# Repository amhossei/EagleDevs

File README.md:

# EagleDevs
Repository of my Eagle developments

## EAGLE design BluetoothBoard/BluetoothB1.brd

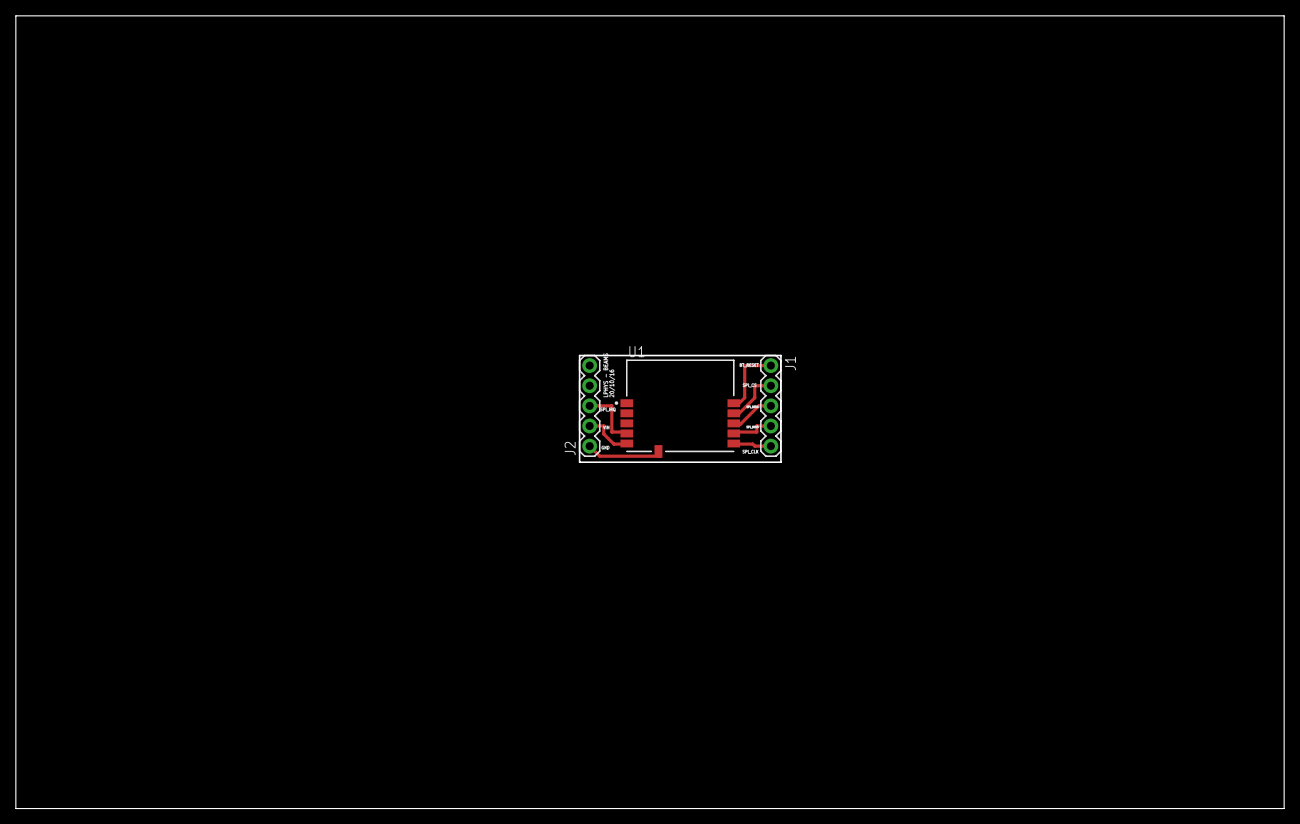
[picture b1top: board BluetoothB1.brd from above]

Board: 2 copper layers, 160.0 x 100.0 mm, 3 parts (0 on the bottom side), 8 nets.

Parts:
J1, J2: 1X05
U1: SPBTLE-RF; XCVR_SPBTLE-RF

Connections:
GND: J2.1, U1.6
unnamed: J1.5, U1.7
unnamed: J1.3, U1.9
unnamed: J1.2, U1.10
unnamed: J1.1, U1.11
unnamed: J2.2, U1.5
unnamed: J2.3, U1.4
SPIMISO: J1.4, U1.8

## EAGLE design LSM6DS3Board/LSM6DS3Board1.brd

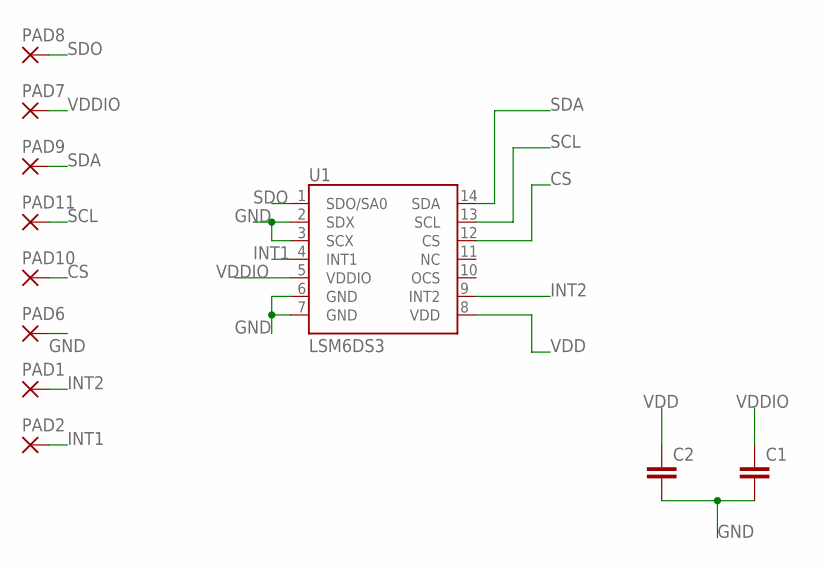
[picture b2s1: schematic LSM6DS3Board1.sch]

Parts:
C1, C2: C-EUC0603; C0603
PAD1, PAD2, PAD6, PAD7, PAD8, PAD9, PAD10, PAD11: 1,6/0,8
U1: LSM6DS3; LGA14L

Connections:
CS: PAD10.1, U1.12 (CS)
GND: C1.2, C2.2, PAD6.1, U1.2 (SDX), U1.3 (SCX), U1.6 (GND), U1.7 (GND)
INT1: PAD2.1, U1.4 (INT1)
INT2: PAD1.1, U1.9 (INT2)
SCL: PAD11.1, U1.13 (SCL)
SDA: PAD9.1, U1.14 (SDA)
SDO: PAD8.1, U1.1 (SDO/SA0)
VDD: C2.1, U1.8 (VDD)
VDDIO: C1.1, PAD7.1, U1.5 (VDDIO)

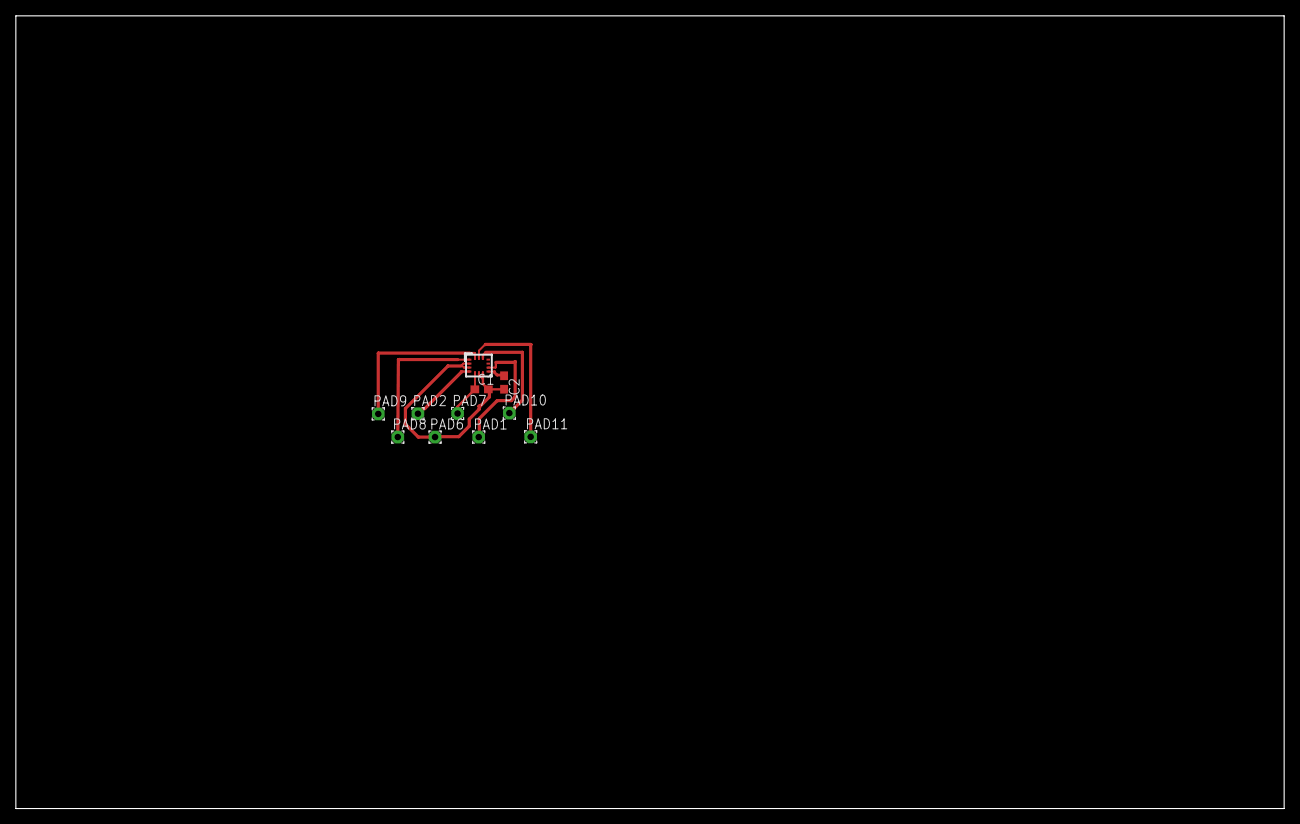
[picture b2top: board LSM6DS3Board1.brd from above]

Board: 2 copper layers, 160.0 x 100.0 mm, 11 parts (0 on the bottom side), 9 nets.

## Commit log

2016-10-14 first empty projects added
2016-10-19 add bluetooth board completed
2016-10-20 created complete LSM6DS3 implementation + configured Bluetooth to be printed

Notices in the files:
parts and their libraries:
SparkFun-Connectors: Licensing: Creative Commons ShareAlike 4.0 International - https://creativecommons.org/licenses/by-sa/4.0
